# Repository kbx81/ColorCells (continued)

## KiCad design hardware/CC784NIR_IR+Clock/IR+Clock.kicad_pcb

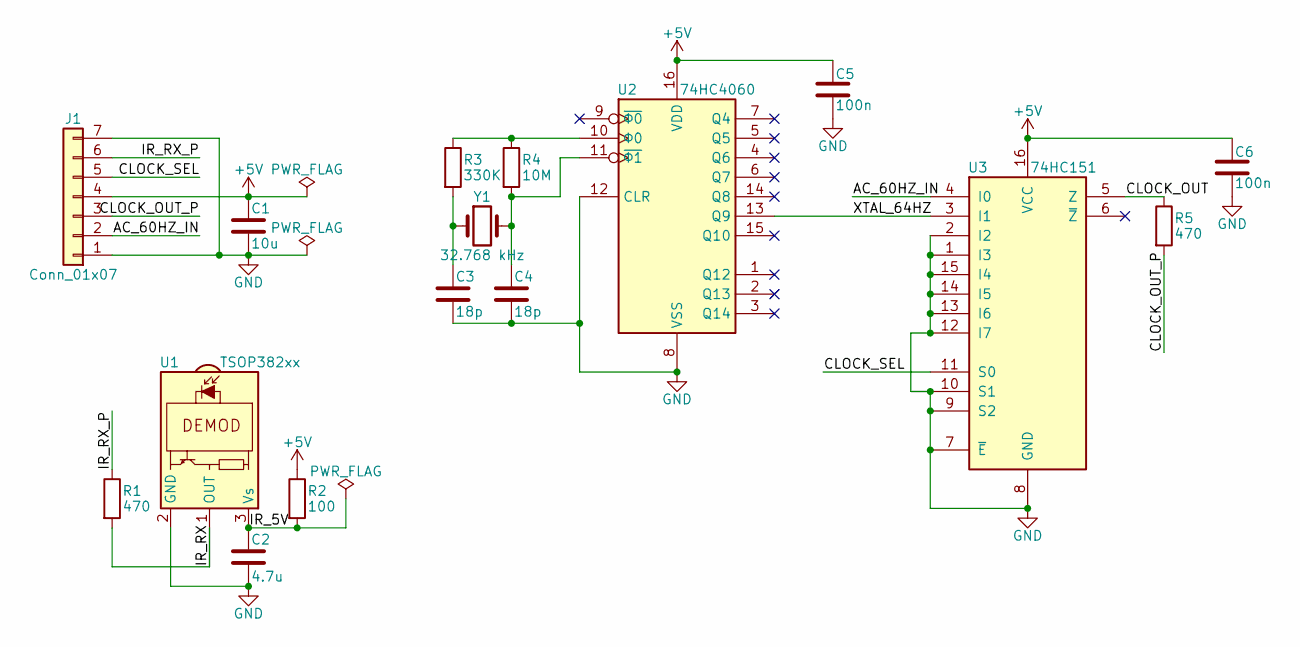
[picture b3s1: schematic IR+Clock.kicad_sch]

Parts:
C1: 10u; C_0805_2012Metric_Pad1.18x1.45mm_HandSolder; MPN1 C2012X5R1C106M085AC
C2: 4.7u; C_0805_2012Metric_Pad1.18x1.45mm_HandSolder; MPN1 C2012X7R1H475K125AE
C3, C4: 18p; C_0805_2012Metric_Pad1.18x1.45mm_HandSolder; MPN1 C0805C180J5GACTU
C5, C6: 100n; C_0805_2012Metric_Pad1.18x1.45mm_HandSolder; MPN1 CC0805KRX7R9BB104
J1: Conn_01x07; PinHeader_1x07_P2.54mm_Horizontal
R1, R5: 470; R_0805_2012Metric_Pad1.20x1.40mm_HandSolder; MPN1 RC0805FR-07470RL
R2: 100; R_0805_2012Metric_Pad1.20x1.40mm_HandSolder; MPN1 RC0805JR-07100RL
R3: 330K; R_0805_2012Metric_Pad1.20x1.40mm_HandSolder; MPN1 RC0805FR-07330KL
R4: 10M; R_0805_2012Metric_Pad1.20x1.40mm_HandSolder; MPN1 RC0805FR-0710ML
U1: TSOP382xx; Vishay_MINICAST-3Pin; MPN1 TSOP38230
U2: 74HC4060; DIP-16_W7.62mm; MPN1 CD74HC4060E
U3: 74HC151; DIP-16_W7.62mm; MPN1 SN74HC151N
Y1: 32.768 kHz; Crystal_C26-LF_D2.1mm_L6.5mm_Horizontal; MPN1 ECS-.327-12.5-13X-C

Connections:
+5V: C1.1, C5.1, C6.1, J1.4, R2.1, U2.16 (VDD), U3.16 (VCC)
/AC_60HZ_IN: J1.2, U3.4 (I0)
/CLOCK_OUT: R5.1, U3.5 (Z)
/CLOCK_OUT_P: J1.3, R5.2
/CLOCK_SEL: J1.5, U3.11 (S0)
/IR_5V: C2.1, R2.2, U1.3 (Vs)
/IR_RX: R1.2, U1.1 (OUT)
/IR_RX_P: J1.6, R1.1
/XTAL_64HZ: U2.13 (Q9), U3.3 (I1)
GND: C1.2, C2.2, C3.2, C4.2, C5.2, C6.2, J1.1, J1.7, U1.2 (GND), U2.8 (VSS), U2.12 (CLR), U3.1 (I3), U3.2 (I2), U3.7 (~E), U3.8 (GND), U3.9 (S2), U3.10 (S1), U3.12 (I7), U3.13 (I6), U3.14 (I5), U3.15 (I4)
unnamed: C3.1, R3.2, Y1.1
unnamed: C4.1, R4.2, U2.11 (~Φ1), Y1.2
unnamed: R3.1, R4.1, U2.10 (Φ0)

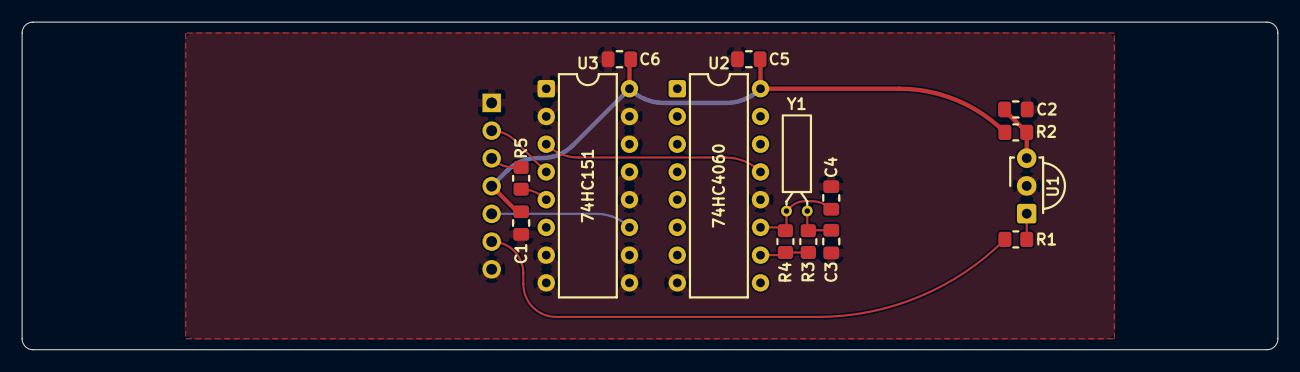
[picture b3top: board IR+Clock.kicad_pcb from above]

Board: 2 copper layers, 115.0 x 30.0 mm, 16 parts (1 on the bottom side), 13 nets.
